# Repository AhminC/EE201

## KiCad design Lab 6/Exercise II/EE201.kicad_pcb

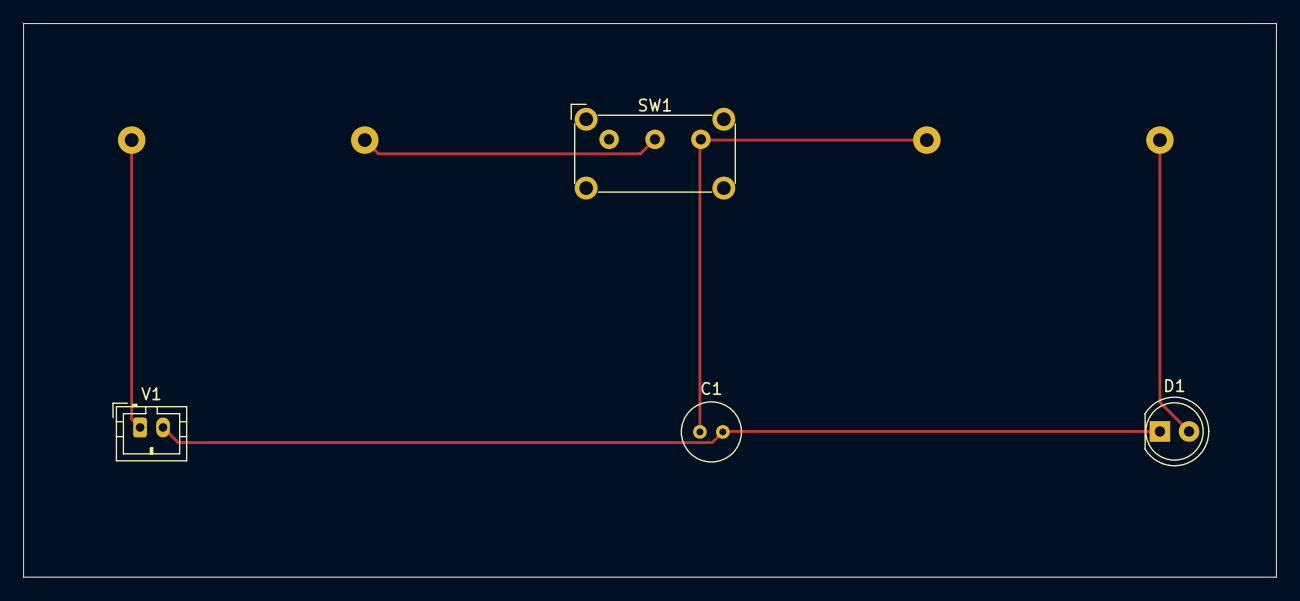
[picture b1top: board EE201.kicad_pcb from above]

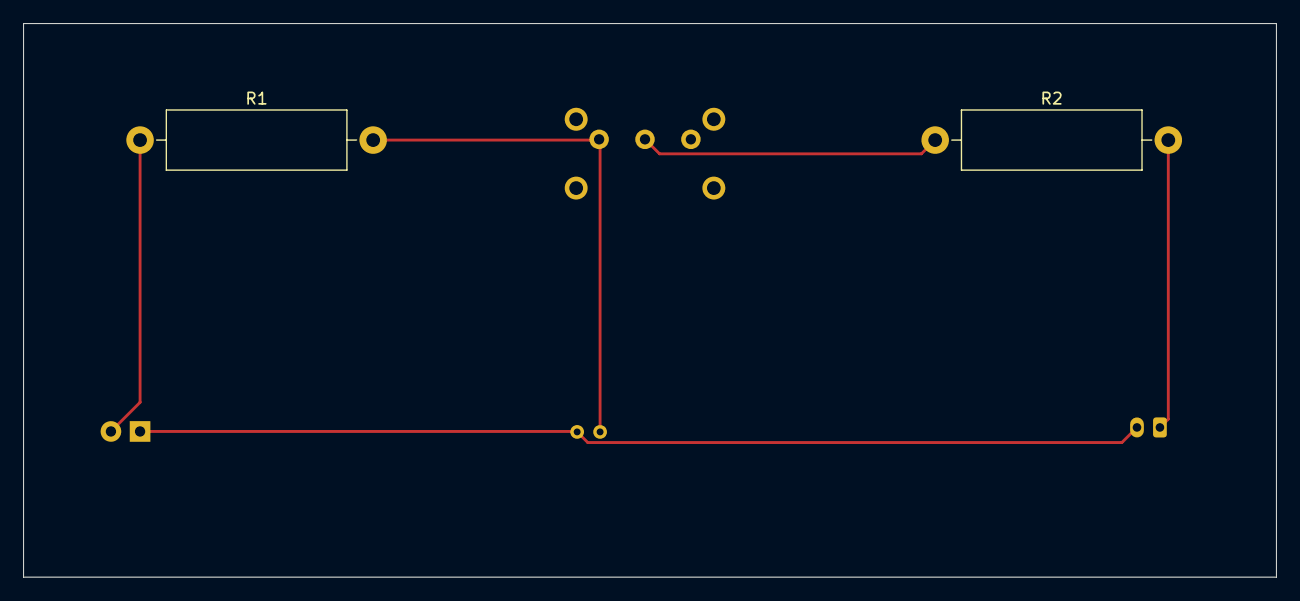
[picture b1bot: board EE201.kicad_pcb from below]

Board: 2 copper layers, 109.2 x 48.3 mm, 6 parts (2 on the bottom side), 5 nets.

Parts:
C1: 4.7 nanF; C_Radial_D5.0mm_H5.0mm_P2.00mm
D1: LED; LED_D5.0mm
R1: 20 kOhms; R_Axial_DIN0516_L15.5mm_D5.0mm_P20.32mm_Horizontal
R2: 2.2 kOhms; R_Axial_DIN0516_L15.5mm_D5.0mm_P20.32mm_Horizontal
SW1: SW_SPDT; SW_E-Switch_EG1224_SPDT_Angled
V1: 9V; JST_PH_B2B-PH-K_1x02_P2.00mm_Vertical

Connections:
unnamed: C1.2, D1.1 (K), V1.2
unnamed: D1.2 (A), R1.1
unnamed: C1.1, R1.2, SW1.3 (C)
unnamed: R2.1, SW1.2 (B)
unnamed: R2.2, V1.1

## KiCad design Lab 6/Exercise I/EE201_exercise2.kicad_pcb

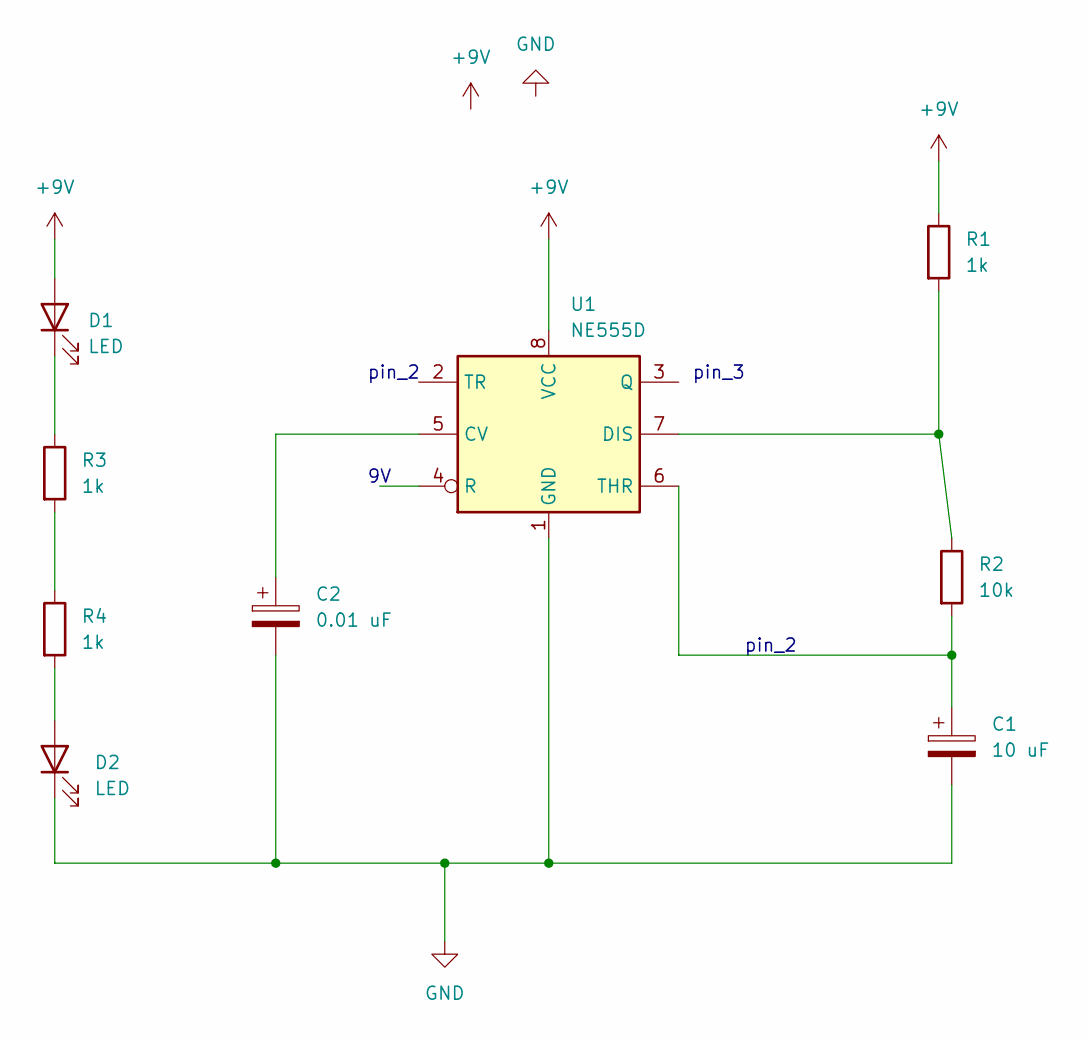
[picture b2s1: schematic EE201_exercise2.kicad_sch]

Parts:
C1: 10 uF
C2: 0.01 uF
D1, D2: LED
R1, R3, R4: 1k
R2: 10k
U1: NE555D; SOIC-8_3.9x4.9mm_P1.27mm

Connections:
+9V: D1.2 (A), R1.1, U1.8 (VCC)
GND: C1.2, C2.2, D2.1 (K), U1.1 (GND)
unnamed: C1.1, R2.2, U1.6 (THR)
unnamed: C2.1, U1.5 (CV)
unnamed: D1.1 (K), R3.1
unnamed: D2.2 (A), R4.2
unnamed: R1.2, R2.1, U1.7 (DIS)
unnamed: R3.2, R4.1

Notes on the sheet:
pin_3
pin_2
pin_2

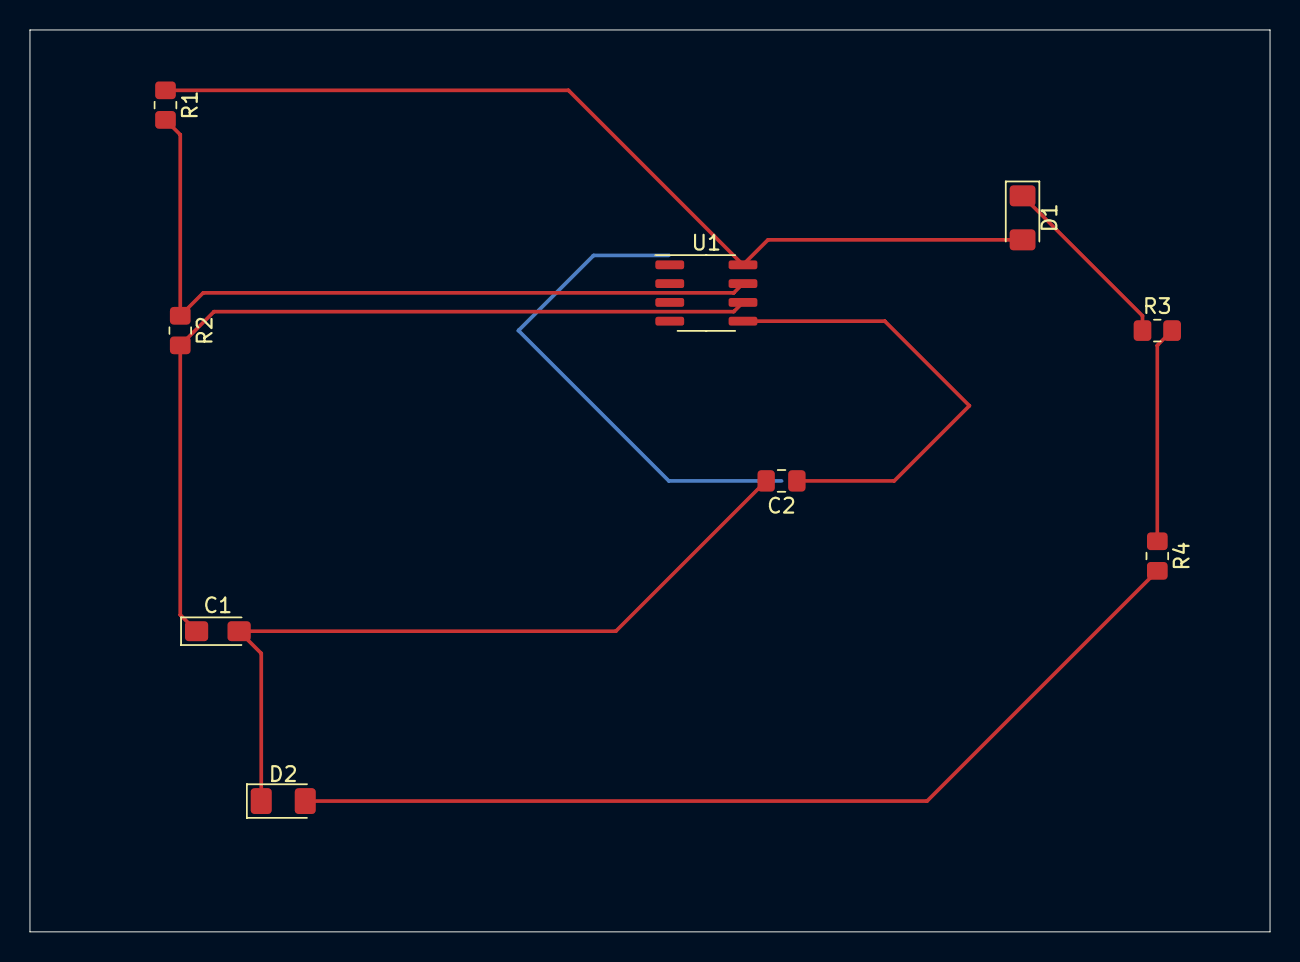
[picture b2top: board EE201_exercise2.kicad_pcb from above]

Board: 2 copper layers, 83.8 x 61.0 mm, 9 parts (0 on the bottom side), 8 nets.

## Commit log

2023-01-12 Added read me
2023-01-12 test
2023-01-19 Create test
2023-01-20 Rename EE201_EXERCISE2.ino to Lab 3 Arduino Exercises/EE201_EXERCISE2.ino
2023-01-20 Rename EE201_EXERCISE3.ino to Lab 3 Arduino Exercises/EE201_EXERCISE3.ino
2023-01-20 Rename EE201_EXERCISE4.ino to Lab 3 Arduino Exercises/EE201_EXERCISE4.ino
2023-01-26 Rename EE201_exercise1.kicad_sch to Lab 4 PCB/EE201_exercise1.kicad_sch
2023-01-26 Rename EE201_exercise2.kicad_sch to Lab 4 PCB/EE201_exercise2.kicad_sch
2023-02-02 Rename line_drawer.sv to Lab 5/line_drawer.sv
2023-02-09 Create 1
2023-02-09 Rename EE201_exercise2.kicad_pcb to EE201_exercise1.kicad_pcb
2023-02-09 Create as
